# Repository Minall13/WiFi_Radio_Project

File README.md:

# Wi-Fi Radio Project

A standalone touchscreen Internet radio built around the ESP32-S3, with a curated UK station library, live programme metadata, custom carrier PCB and a fully 3D-printed enclosure.

The Wi-Fi Radio Project was developed from an initial ESP32 prototype into a complete self-contained radio. The hardware, firmware, user interface, station catalogue, artwork pipeline, PCB and enclosure have all been developed specifically for the project.

The finished radio is designed to behave as an appliance: switch it on, select a station and listen.

---

## Features

- 4-inch 480 × 320 colour touchscreen interface
- ESP32-S3 with 16 MB Flash and 8 MB PSRAM
- Curated UK Internet radio station library
- BBC and commercial radio support
- Live ICY track metadata
- BBC programme metadata
- Station artwork
- Dual-mono audio using two MAX98357A I²S amplifier modules
- Two 3 W / 4 Ω speakers
- Custom carrier PCB
- USB-C power and firmware programming
- Wi-Fi configuration
- Local station catalogue and artwork stored in LittleFS
- Automatic Station Library Builder
- Fully 3D-printable enclosure

---

## User Interface

The radio uses a purpose-built touchscreen interface rather than a generic ESP32 menu system.

Stations are organised into simple groups such as BBC, Absolute, Virgin, Capital, Heart, Kiss, Rock and Talk, with an **All** option providing access to the complete catalogue.

The Player screen displays the current station, programme or track information and station artwork, together with controls for navigation, stop, volume and mute.

The startup sequence initialises the filesystem, connects to Wi-Fi, prepares BBC programme information and starts the audio subsystem before presenting the radio for use.

---

## Hardware

### Controller

The radio is based around an **ESP32-S3 DevKitC-1 N16R8**:

- 16 MB Flash
- 8 MB PSRAM
- Wi-Fi
- Dual-core ESP32-S3 processor

### Display

- 4-inch 480×320 SPI TFT display, sold as ILI9488 and configured with TFT_eSPI using `ILI9481_DRIVER`
- XPT2046 resistive touchscreen

### Audio

Dual-mono audio is provided by:

- 2 × MAX98357A I²S Class-D amplifier modules
- 2 × 3 W / 4 Ω full-range speakers

### Carrier PCB

A custom KiCad-designed carrier PCB connects the ESP32-S3, display, audio modules, power switching and external USB-C connection.

The PCB was designed specifically for the finished radio and manufactured as part of the project.

The proven Rev A PCB can be ordered directly from the [Wi-Fi Radio Project page on PCBWay](https://www.pcbway.com/project/shareproject/Wi_Fi_Radio_Project_ESP32_S3_Main_PCB_076f3c4a.html).

The rear-panel USB-C connection provides both normal 5 V power and access to the ESP32-S3 USB interface, allowing firmware to be uploaded without dismantling the radio.

PCB design files and manufacturing Gerbers are provided in the `Hardware/` directory.

### Enclosure

The enclosure is fully 3D printed and consists of three principal components:

- Main case
- Face frame
- Base

STL files are provided in this repository for slicer-independent printing.

A Bambu Studio 3MF project, including the complete assembly and individual printable components, is available on [MakerWorld](https://makerworld.com/en/models/3243705-wi-fi-radio-project#profileId-3675408).

The files are located in:

`3D_Files/`

---

## Bill of Materials

A complete parts list for one radio is provided in:

**[BOM.md](BOM.md)**

The BOM includes quantities and example sources for the components used in the original build.

Equivalent components may be used where their electrical and mechanical specifications are compatible.

---

## Software Architecture

The firmware is divided into independent subsystems with clearly defined responsibilities.

```text
Station Library Builder
        │
        ▼
LittleFS Catalogue
        │
        ▼
Station Provider
        │
        ▼
User Interface
        │
        ▼
Player
        │
        ├───────────────┐
        ▼               ▼
Audio Engine     BBC Metadata
        │
        ▼
I²S Audio
        │
        ▼
2 × MAX98357A
```

This separation keeps the user interface, station data, metadata handling and audio playback largely independent of one another.

More detailed design information is available in the `docs/` directory.

---

## Station Library

Rather than querying an Internet radio directory every time the radio starts, the project uses a curated UK station catalogue generated offline.

The **Station Library Builder**:

- validates station definitions;
- selects preferred production streams;
- generates the station catalogues;
- obtains and prepares station artwork;
- generates default artwork where required;
- prepares the files for deployment to LittleFS.

The ESP32 therefore operates from its own local catalogue during normal use.

This makes the radio independent of a live station-directory service while it is operating.

---

## Metadata

Commercial stations primarily use **ICY metadata** supplied by their audio streams.

BBC stations are handled separately using BBC programme metadata, allowing the Player screen to display the programme currently being broadcast.

---

## Station Artwork

Station artwork is stored as PNG images in LittleFS and displayed on the Player screen.

The artwork pipeline can obtain station artwork, apply curated replacements where necessary, generate appropriately sized images and provide default artwork for stations without suitable source material.

> Station names, logos and other third-party branding remain the property of their respective owners. Third-party station artwork is not intended to imply affiliation with or endorsement of this project.

---

## Repository Structure

    WiFi_Radio_Project/
    │
    ├── 3D_Files/                       3D-printable enclosure files
    ├── Hardware/                       KiCad PCB design and manufacturing files
    ├── data/                           Station catalogue and runtime assets
    │   ├── branding/
    │   ├── catalogues/
    │   ├── fonts/
    │   ├── icons/
    │   └── logos/
    ├── docs/                           Project documentation
    ├── images/                         Documentation images
    ├── tools/                          Build and asset-generation utilities
    │   ├── Icon_Builder/
    │   └── Station_Library_Builder/
    │
    ├── WiFi_Radio_Project.ino	        Main Arduino sketch
    ├── partitions.csv                  ESP32 flash partition layout
    ├── deploy                          LittleFS deployment helper
    ├── BOM.md                          Bill of materials
    └── README.md

The remaining numbered `.ino` files in the project root contain the supporting firmware modules.

---

## Building the Radio

The repository contains the principal resources required to reproduce the project:

1. Firmware source
2. Bill of materials
3. KiCad PCB design
4. PCB manufacturing Gerbers
5. 3D-printable enclosure
6. Station Library Builder
7. Supporting documentation

The project was developed and tested using the specific hardware listed in the BOM. Substituting components may require changes to the PCB, enclosure, firmware configuration or pin assignments.

---

## Project Status

**Version 1.0.1**

The Wi-Fi Radio Project has reached its first complete hardware and software release.

The v1.0.1 system includes:

- completed touchscreen user interface;
- curated UK station library;
- streaming audio engine;
- BBC programme metadata;
- ICY metadata;
- station artwork pipeline;
- custom carrier PCB;
- USB-C power and programming;
- dual-mono amplifier and speaker system;
- finished 3D-printed enclosure.

The radio has been assembled and tested as a complete standalone unit.

---

## Documentation

Additional technical documentation is available in the [`docs/`](docs/) directory, covering subjects including:

- system architecture;
- audio;
- display;
- touchscreen;
- operation;
- station catalogue generation;
- artwork and fonts;
- hardware design;
- project history.

---

## Third-Party Components and Services

This project uses a number of third-party open-source libraries, hardware modules and Internet services.

Radio station names and trademarks belong to their respective owners.

Availability and format of Internet radio streams and external metadata services can change independently of this project.

---

## Licence

The Wi-Fi Radio Project uses a mixed licensing model.

Original project software is licensed under the **PolyForm Noncommercial License 1.0.0**.

Original hardware designs, PCB files, 3D-printable models, documentation and project photographs are licensed under the **Creative Commons Attribution-NonCommercial 4.0 International (CC BY-NC 4.0)** licence.

These licences permit personal, non-commercial use, modification and redistribution subject to their respective terms and attribution requirements. Commercial use of the original project material is not permitted without separate permission from the copyright holder.

Third-party components and assets remain subject to their own licences.

See [`LICENSE.md`](LICENSE.md) for the complete licensing details and attribution requirements.

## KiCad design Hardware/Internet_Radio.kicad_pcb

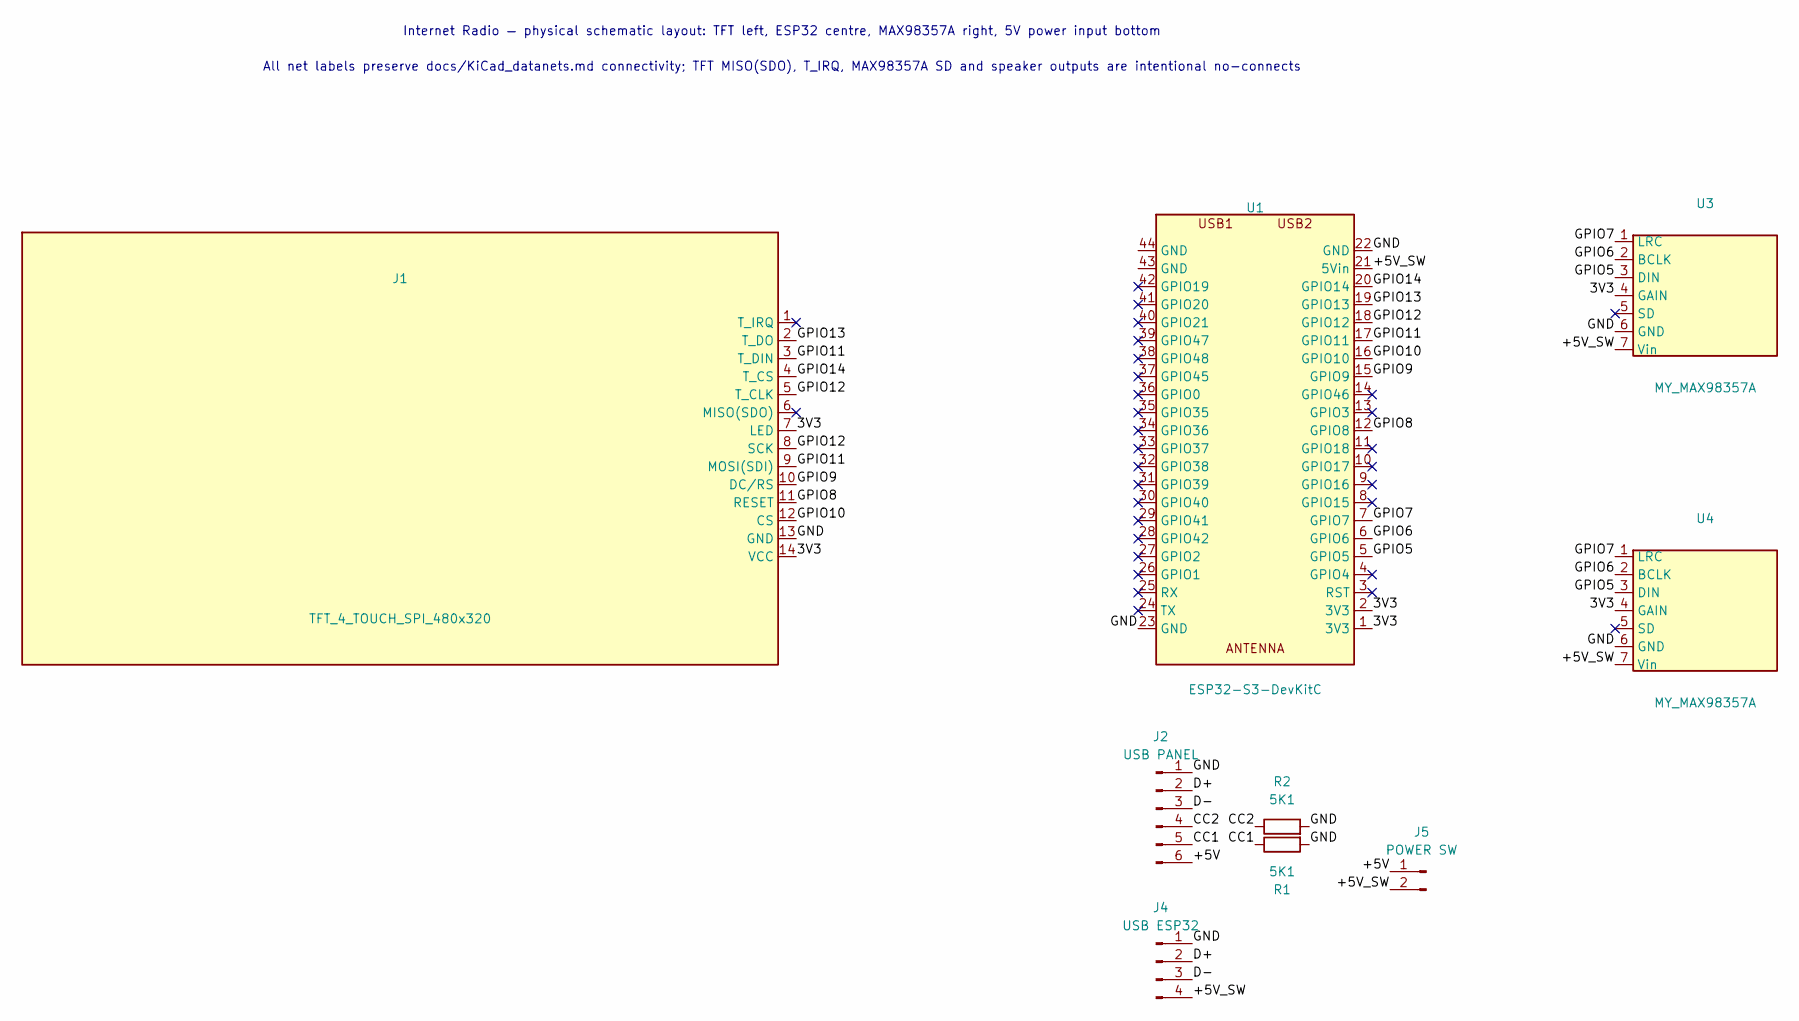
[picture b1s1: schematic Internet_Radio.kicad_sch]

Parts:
J1: TFT_4_TOUCH_SPI_480x320; TFT_4_TOUCH_SPI_480x320_PNG
J2: USB PANEL; JST_PH_B6B-PH-K_1x06_P2.00mm_Vertical
J4: USB ESP32; JST_XH_B4B-XH-A_1x04_P2.50mm_Vertical
J5: POWER SW; JST_XH_B2B-XH-A_1x02_P2.50mm_Vertical
R1, R2: 5K1; R_0603_1608Metric
U1: ESP32-S3-DevKitC; ESP32-S3-DevKitC_PNG
U3, U4: MY_MAX98357A; MY_MAX98357A_PNG

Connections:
/3V3: J1.7 (LED), J1.14 (VCC), U1.1 (3V3), U1.2 (3V3), U3.4 (GAIN), U4.4 (GAIN)
/+5V: J2.6, J5.1
/+5V_SW: J4.4, J5.2, U1.21 (5Vin), U3.7 (Vin), U4.7 (Vin)
/CC1: J2.5, R1.1
/CC2: J2.4, R2.1
/D+: J2.2, J4.2
/D-: J2.3, J4.3
/GND: J1.13 (GND), J2.1, J4.1, R1.2, R2.2, U1.22 (GND), U1.23 (GND), U3.6 (GND), U4.6 (GND)
/GPIO5: U1.5 (GPIO5), U3.3 (DIN), U4.3 (DIN)
/GPIO6: U1.6 (GPIO6), U3.2 (BCLK), U4.2 (BCLK)
/GPIO7: U1.7 (GPIO7), U3.1 (LRC), U4.1 (LRC)
/GPIO8: J1.11 (RESET), U1.12 (GPIO8)
/GPIO9: J1.10 (DC/RS), U1.15 (GPIO9)
/GPIO10: J1.12 (CS), U1.16 (GPIO10)
/GPIO11: J1.3 (T_DIN), J1.9 (MOSI(SDI)), U1.17 (GPIO11)
/GPIO12: J1.5 (T_CLK), J1.8 (SCK), U1.18 (GPIO12)
/GPIO13: J1.2 (T_DO), U1.19 (GPIO13)
/GPIO14: J1.4 (T_CS), U1.20 (GPIO14)

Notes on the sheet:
All net labels preserve docs/KiCad_datanets.md connectivity; TFT MISO(SDO), T_IRQ, MAX98357A SD and speaker outputs are intentional no-connects
Internet Radio — physical schematic layout: TFT left, ESP32 centre, MAX98357A right, 5V power input bottom

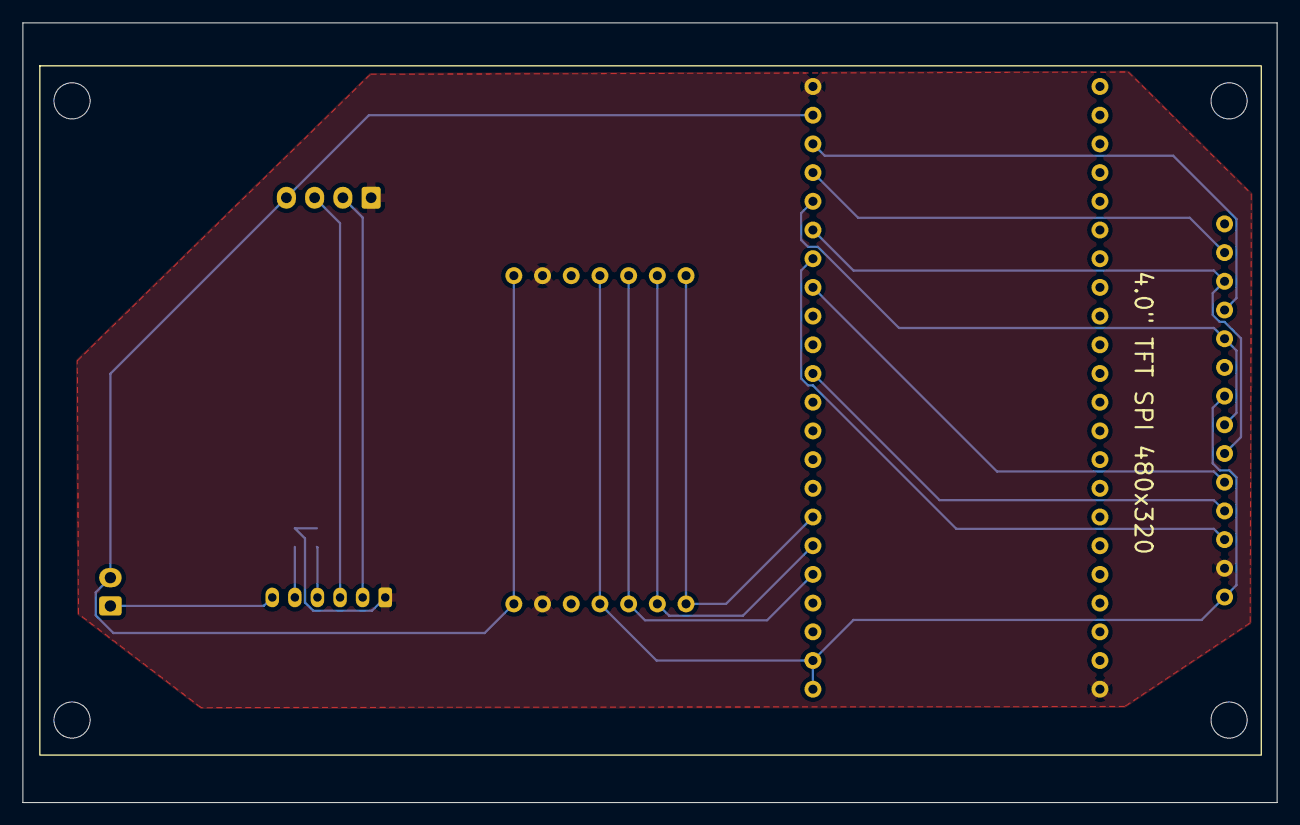
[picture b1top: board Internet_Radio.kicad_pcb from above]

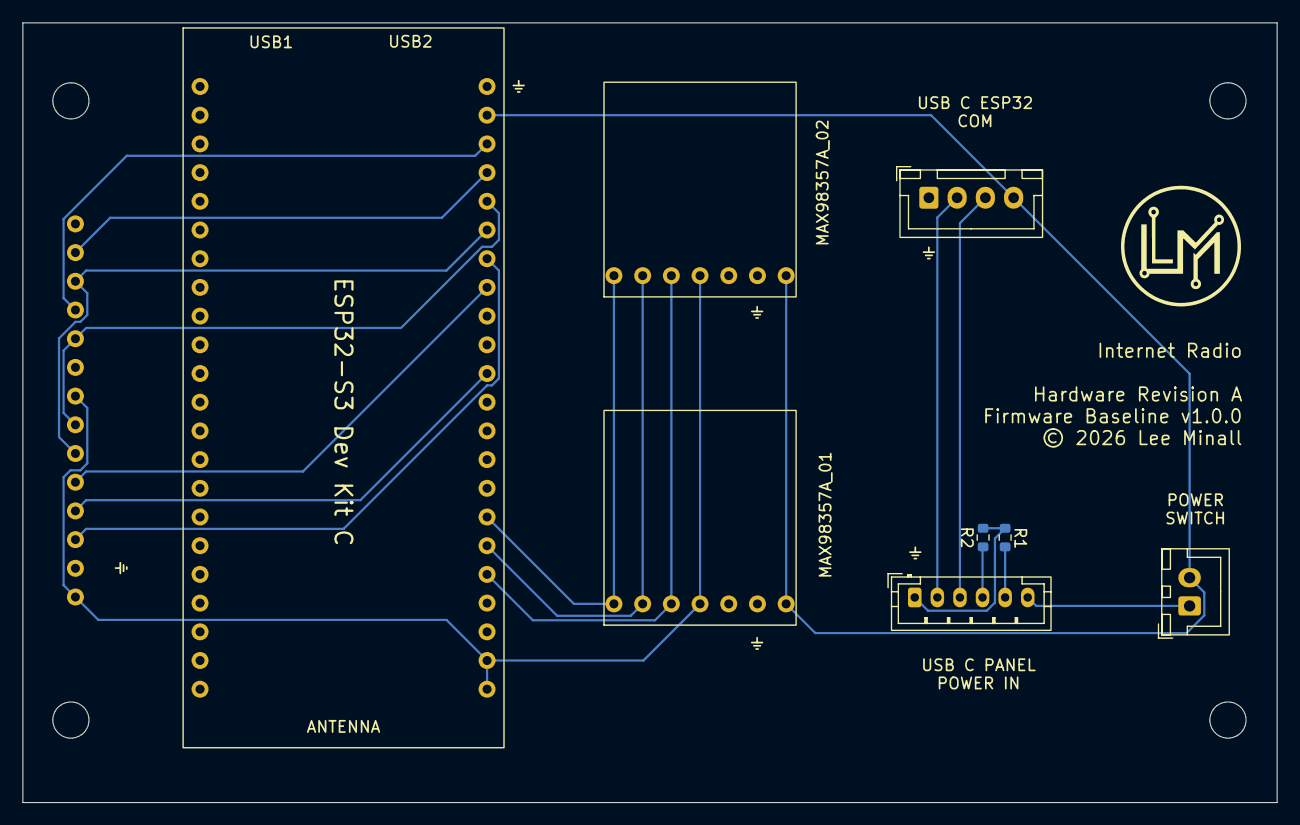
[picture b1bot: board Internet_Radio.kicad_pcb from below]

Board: 2 copper layers, 111.0 x 69.0 mm, 9 parts (8 on the bottom side), 18 nets.

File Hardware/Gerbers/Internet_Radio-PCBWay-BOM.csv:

Designator,Quantity,Value,Manufacturer Part Number,Description,Package,Substitution
J2,1,USB PANEL,B6B-PH-K-S,"6-pin vertical JST-PH connector, 2.00 mm pitch","JST PH 1x06 Vertical","Compatible equivalent permitted; identical pin count, pitch and PCB footprint required"
J4,1,USB ESP32,B4B-XH-A,"4-pin vertical JST-XH connector, 2.50 mm pitch","JST XH 1x04 Vertical","Compatible equivalent permitted; identical pin count, pitch and PCB footprint required"
J5,1,POWER SW,B2B-XH-A,"2-pin vertical JST-XH connector, 2.50 mm pitch","JST XH 1x02 Vertical","Compatible equivalent permitted; identical pin count, pitch and PCB footprint required"
R1 R2,2,5.1k,Generic,"5.1 kOhm resistor, 1%","0603 (1608 metric)","Any reputable equivalent permitted"

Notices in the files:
Hardware/Internet_Radio.kicad_pcb:
© 2026 Lee Minall
